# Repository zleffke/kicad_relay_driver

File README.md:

# kicad_relay_driver
KiCAD design for running 24V coax relays from a 12V source.

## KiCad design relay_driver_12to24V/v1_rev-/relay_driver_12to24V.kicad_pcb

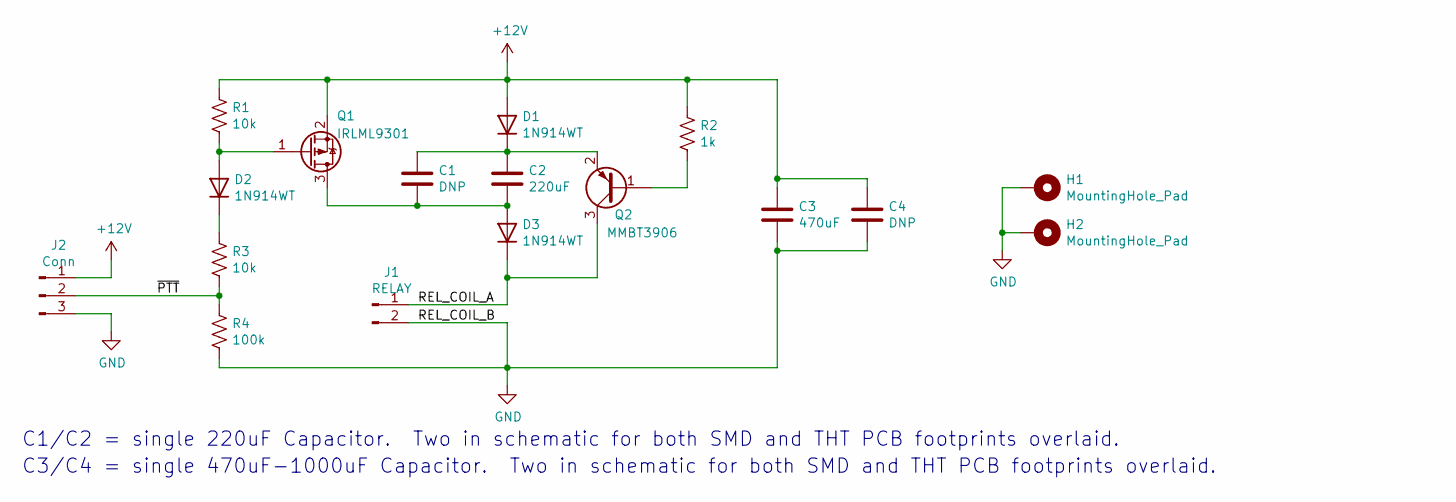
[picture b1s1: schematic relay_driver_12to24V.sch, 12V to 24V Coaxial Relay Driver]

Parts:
C1: DNP; CP_Elec_8x10.5
C2: 220uF; CP_Radial_D8.0mm_P3.50mm
C3: 470uF; CP_Elec_10x10
C4: DNP; CP_Radial_D10.0mm_P5.00mm
D1, D2, D3: 1N914WT; D_SOD-523
H1, H2: MountingHole_Pad; MountingHole_2.5mm_Pad_Via
J1: RELAY; PinHeader_1x02_P2.54mm_Vertical
J2: Conn; PinHeader_1x03_P2.54mm_Vertical
Q1: IRLML9301; SOT-23
Q2: MMBT3906; SOT-23
R1, R3: 10k; 0805
R2: 1k; 0805
R4: 100k; 0805

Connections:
+12V: C3.1, C4.1, D1.2 (A), J2.1, Q1.2 (S), R1.1, R2.1
/REL_COIL_A: D3.1 (K), J1.1, Q2.3 (C)
/~PTT: J2.2, R3.2, R4.1
GND: C3.2, C4.2, H1.1, H2.1, J1.2, J2.3, R4.2
unnamed: C1.1, C2.1, D1.1 (K), Q2.2 (E)
unnamed: C1.2, C2.2, D3.2 (A), Q1.3 (D)
unnamed: D2.1 (K), R3.1
unnamed: D2.2 (A), Q1.1 (G), R1.2
unnamed: Q2.1 (B), R2.2

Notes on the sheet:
C1/C2 = single 220uF Capacitor. Two in schematic for both SMD and THT PCB footprints overlaid.
C3/C4 = single 470uF-1000uF Capacitor. Two in schematic for both SMD and THT PCB footprints overlaid.

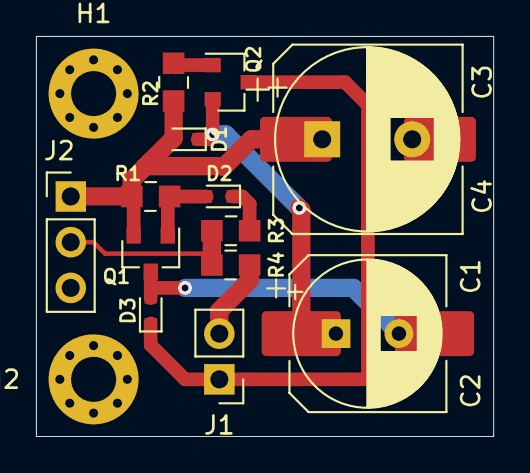
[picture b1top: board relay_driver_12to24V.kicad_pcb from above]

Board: 2 copper layers, 25.4 x 22.2 mm, 17 parts (0 on the bottom side), 9 nets.

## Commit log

2020-06-02 mass commit of completed design. Submitted to osh park on this commit.
2020-06-02 adding osh park board images.
2020-06-09 adding schematic PDF
2021-02-22 mass commit

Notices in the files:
relay_driver_12to24V/v1_rev-/relay_driver_12to24V.sch:
creativecommons.org/licenses/by/4.0
License: CC BY 4.0
